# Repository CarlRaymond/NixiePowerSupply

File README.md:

A KiCad project for a high-voltage Nixie tube power supply.

Adapted from Nick DeSmith's design at http://www.desmith.net/NMdS/Electronics/NixiePSU.html.

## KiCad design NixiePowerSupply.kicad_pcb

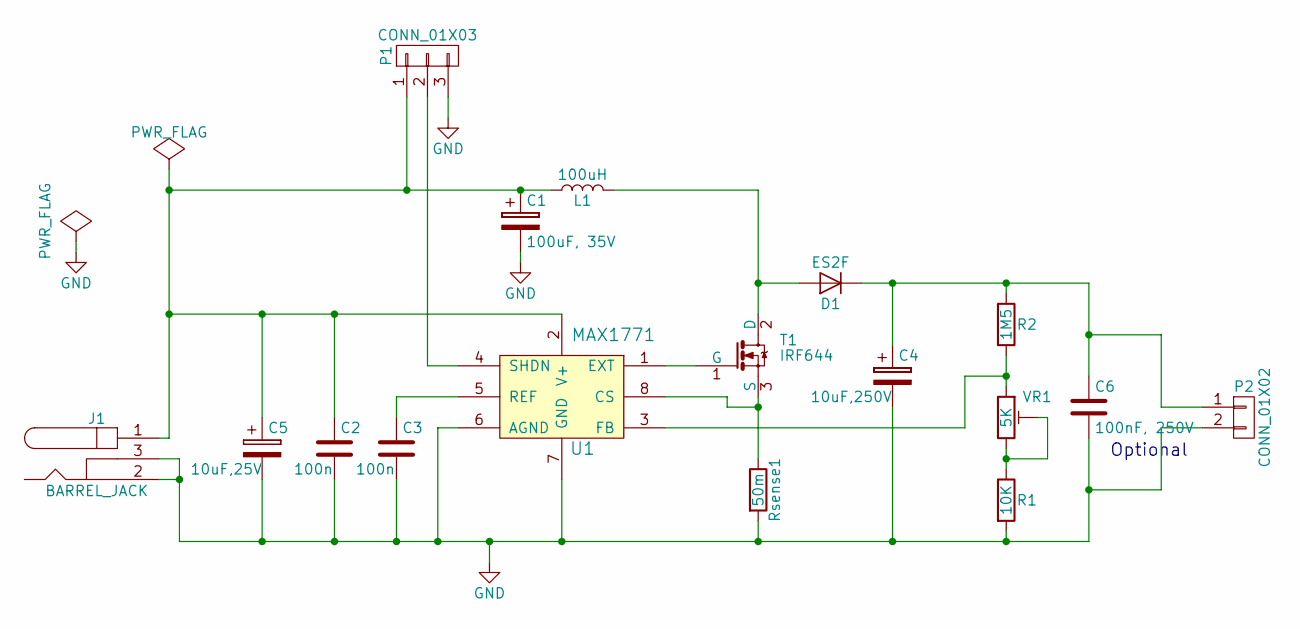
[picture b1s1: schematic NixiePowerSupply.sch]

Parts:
C1: 100uF, 35V; CP_Tantalum_Case-X_EIA-7343-43_Hand
C2, C3: 100n; C_0805_HandSoldering
C4: 10uF,250V; CP_Elec_10x10
C5: 10uF,25V; CP_Tantalum_Case-X_EIA-7343-43_Hand
C6: 100nF, 250V; Panasonic_ECWU_Size_B
D1: ES2F
J1: BARREL_JACK
L1: 100uH; L-B82479A1
P1: CONN_01X03; Pin_Header_Straight_1x03_Pitch2.54mm
P2: CONN_01X02; Pin_Header_Straight_1x03_Pitch2.54mm_No_Center
R1: 10K; R_0805_HandSoldering
R2: 1M5; R_2512_HandSoldering
Rsense1: 50m; R_2010_HandSoldering
T1: IRF644; TO-220_Vertical
U1: MAX1771; SOIC-8_3.9x4.9mm_Pitch1.27mm
VR1: 5K; Trimpot_Bourns_3214W

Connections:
GND: C1.2, C2.2, C3.2, C4.2, C5.2, C6.2, J1.2, J1.3, P1.3, P2.2, R1.2, Rsense1.2, U1.6 (AGND), U1.7 (GND)
unnamed: C1.1, C2.1, C5.1, J1.1, L1.1, P1.1, U1.2 (V+)
unnamed: C3.1, U1.5 (REF)
unnamed: C4.1, C6.1, D1.1 (K), P2.1, R2.1
unnamed: D1.2 (A), L1.2, T1.2 (D)
unnamed: P1.2, U1.4 (SHDN)
unnamed: R1.1, VR1.2, VR1.3
unnamed: R2.2, U1.3 (FB), VR1.1
unnamed: Rsense1.1, T1.3 (S), U1.8 (CS)
unnamed: T1.1 (G), U1.1 (EXT)

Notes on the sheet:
Optional

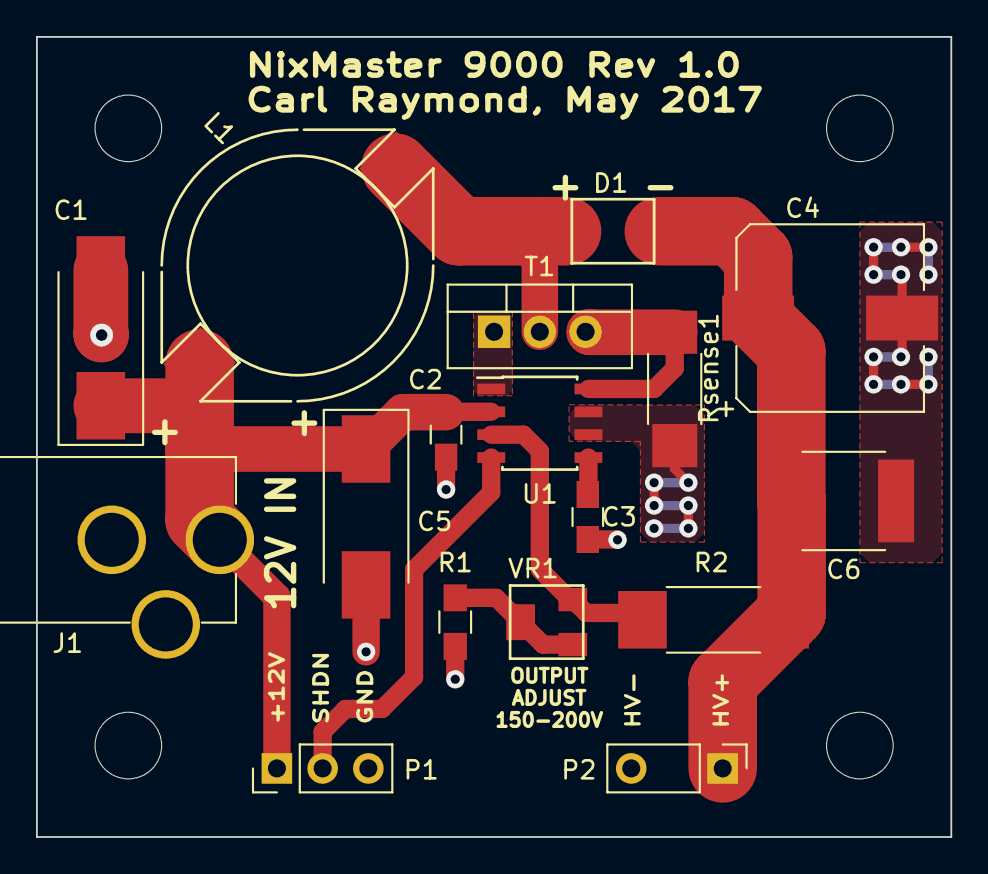
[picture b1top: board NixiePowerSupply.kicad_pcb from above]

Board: 2 copper layers, 50.8 x 44.4 mm, 17 parts (0 on the bottom side), 10 nets.

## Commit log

2017-03-26 Initial checkin.
2017-03-26 Preliminary schematic capture
2017-03-26 Add output capcacitor
2017-03-27 Assigned some footprints.
2017-03-28 Add project footprint libary; start layout
2017-03-29 Added cap and trimpot footprints
2017-03-29 Add headers
2017-03-30 More layout; add trimpot model
2017-03-31 Added some tracks.
2017-04-01 Finished routing
2017-04-03 Board re-layout
2017-04-10 Fixed output connector
2017-04-20 More fiddling with via stitching
2017-04-21 Fix via stitching
2017-04-21 Added Gerber extensions to .gitignore
2017-04-25 Trying to make a new board
2017-04-25 Footprints place; partially routed
2017-04-26 More layout
2017-04-27 Added mounting holes
2017-04-28 Embiggened the board
2017-05-03 Routing complete
2017-05-04 Add 3D model for trimpot. Still not right.
2017-05-04 Added missing C1
2017-05-05 Add barrel jack model
2017-05-06 Added B82479 models
2017-05-06 Add 3D model for B82479; generate output files
2017-05-07 Changed 12V jack to round-hole version
2017-05-08 Updated 3D rendering
